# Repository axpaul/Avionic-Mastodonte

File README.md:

# Mastodonte – Séquenceur

**Mastodonte** est un ordinateur de bord, ou plus précisément un **séquenceur**, destiné à orchestrer de manière autonome les événements critiques d’un vol de fusée expérimentale. Il est conçu pour répondre aux exigences du **cahier des charges du C'Space**, et s’intègre à tout projet nécessitant un séquencement fiable, robuste et temps réel.

---

> *© 2025/2026 - Paul Miailhe.*  
> *This material is licensed under the CERN Open Hardware Licence Version 2 - Strongly Reciprocal (CERN-OHL-S). [→ CERN-OHL-S](https://ohwr.org/licences/)*
> > 

---

---

## Fonctionnement

Mastodonte supervise et déclenche en toute autonomie les étapes clés du vol, sans intervention extérieure :

### Détection du décollage
La détection initiale peut se faire par deux méthodes :
- Un **contact jack** (fil coupe-circuit) : un câble fin relie la fusée au sol, et se sectionne au moment du lancement. La coupure génère une interruption matérielle, qui marque le T-0 du vol.
- Un **accéléro-contact** (contacteur à masselotte) peut également déclencher le séquenceur dès détection d’une accélération.

Dans les deux cas, la carte démarre son chronomètre interne pour initier la séquence.

### Fenêtrage temporel autour de l’apogée
Après le décollage, Mastodonte ouvre une **fenêtre temporelle** durant laquelle la détection de l’apogée est autorisée :
- Un signal extérieur, par exemple issu d’un autre système avionique ou d’un capteur, peut être reçu via un **optocoupleur** pour indiquer l’apogée.
- Ce signal n’est pris en compte **que pendant la fenêtre**, afin d’écarter toute détection parasite en dehors de cette phase critique.
- Si aucune détection n’est reçue, un **déclenchement de sécurité** est effectué après un **temps maximal prédéfini** post-apogée, garantissant ainsi l’ouverture du système de récupération.

### Déploiement du système de récupération
En réponse à une détection d’apogée (ou par sécurité en fin de fenêtre), Mastodonte déclenche le système de récupération :
- Par **charge pyrotechnique** (détonateur, coupe-corde, etc.),
- Ou par **moteur DC** (vis de poussée, libération mécanique, etc.).

### Enregistrement des événements critiques
Mastodonte assure un enregistrement précis des points clés du vol :
- Heure de **décollage** (T-0),
- **Début et fin** de la fenêtre d’apogée,
- **Réception (ou absence)** du signal d’apogée,
- **Déclenchement** du système de récupération,
- **Tension batterie** mesurée durant le vol,
- **Événements d’erreur moteur** détectés.

Ce journal d’exécution agit comme une **boîte noire embarquée**, permettant d’analyser a posteriori le bon déroulement de la mission, et d’identifier toute anomalie de comportement.

---

> Mastodonte vise à offrir un **fonctionnement déterministe**, **fiable** et **autonome**, même en l’absence de télémétrie ou de supervision au sol, conformément à l’esprit du **cahier des charges C'Space**.

---

## Architecture & Fonctionnalités

### Alimentation et protections
- Protection contre l’inversion de polarité (MOSFET P **SQD50P04-13L**)
- Protection contre surtensions (**TVS SMAJ14A**)
- Limitation de courant via fusible réarmable
- Régulation de tension (LM340AT : 7.4 V batterie → 5 V)
- Sélection de la source d’alimentation (USB-C ou batterie)
- LED d’indication d’alimentation

### Microcontrôleur RP2040-YD

Mastodonte s’appuie sur la carte **RP2040-YD**, une carte commerciale compacte embarquant un microcontrôleur **RP2040** de Raspberry Pi, accompagnée de ses périphériques essentiels :

- Double cœur **ARM Cortex-M0+** cadencé à 133 MHz
- **128 Mbits (16 MB)** de mémoire flash externe **W25Q128**
- Oscillateur intégré à **12 MHz**
- Interface native **USB-C**
- Format physique compatible **Raspberry Pi Pico**
- Brochage latéral avec **40 broches GPIO** (20 de chaque côté)
- LED RGB **WS2812** intégrée (GPIO23)
- Boutons embarqués :
  - **BOOT**
  - **RESET**
  - **USER KEY** (GPIO24)
- Interface **SWD** pour débogage

La carte **RP2040-YD** est conçue pour venir se **connecter verticalement** sur le PCB principal appelé **BR-Motor** via deux rangées de connecteurs femelles. Une fois assemblée, l'ensemble forme la carte **Mastodonte**, regroupant la logique de contrôle (RP2040-YD) et l’électronique de puissance et d’interface (BR-Motor).

### Interfaces et connectiques
- Connecteurs au format **JST B2B-XH**
- Connexions dédiées pour moteurs, charges pyrotechniques, capteurs et interfaces de communication
- Tensions disponibles : **5 V** et **3.3 V**

---

## Interfaces et E/S

### Commande moteur / Charge pyrotechnique
- 3 drivers **DRV8872DDA** (ponts en H)
  - Jusqu’à **3.6 A** sous **6.5–45 V**
  - Contrôle **PWM**
  - LED de direction pour visualisation sans charge
  - Détection d’erreurs via broche **nFAULT**

### Signaux d’entrée isolés
- **Optocoupleurs ACPL-214** pour isolation galvanique
- Buffers logiques **74HC14** (Schmitt trigger) pour traitement numérique
- Isolation UART et conversion de niveau : **ADuM1281**
- Pull-ups 4.7 kΩ intégrés sur les lignes I²C

### Buzzer de notification
- Pilotage via transistor **BSS138**
- Protection par diode **1N4148**
- Activation par GPIO (IN_BUZZ)

---

## Schéma fonctionnel

---

## Signaux sortants – Carte Mastodonte (RP2040-YD)

| Signal         | Type de signal     | Connecteur        | GPIO RP2040 | Description |
|----------------|--------------------|-------------------|-------------|-------------|
| `IN1_M1`       | PWM / Logique      | J6 (Moteur 1)     | GP14        | Commande H-Bridge moteur/charge 1 |
| `IN2_M1`       | PWM / Logique      | J6 (Moteur 1)     | GP15        | Commande H-Bridge moteur/charge 1 |
| `IN1_M2`       | PWM / Logique      | J7 (Moteur 2)     | GP16        | Commande H-Bridge moteur/charge 2 |
| `IN2_M2`       | PWM / Logique      | J7 (Moteur 2)     | GP17        | Commande H-Bridge moteur/charge 2 |
| `IN1_M3`       | PWM / Logique      | J8 (Moteur 3)     | GP18        | Commande H-Bridge moteur/charge 3 |
| `IN2_M3`       | PWM / Logique      | J8 (Moteur 3)     | GP19         | Commande H-Bridge moteur/charge 3 |
| `IN_BUZZ`      | Logique             | J5 (Buzzer)       | GP2         | Commande du buzzer (MOSFET BSS138) |
| `OUT_N1`       | GPIO                | J10               | GP26        | Sortie numérique non isolée |
| `OUT_N2`       | GPIO                | J10               | GP27        | Sortie numérique non isolée |
| `OUT_N3`       | GPIO                | J10               | GP10        | Sortie numérique non isolée |
| `OUT_N4`       | GPIO                | J11               | GP11        | Sortie numérique non isolée |
| `OUT_N5`       | GPIO                | J11               | GP12        | Sortie numérique non isolée |
| `OUT_N6`       | GPIO                | J11               | GP13        | Sortie numérique non isolée |
| `OUT_ISO_N3`   | GPIO isolée         | J13 (Opto)        | GP3         | Sortie isolée via optocoupleur |
| `OUT_ISO_N4`   | GPIO isolée         | J13 (Opto)        | GP4         | Sortie isolée via optocoupleur |
| `SDA`          | I²C (données)       | J12 (I²C)         | GP8         | Bus I²C données (avec pull-up) |
| `SCL`          | I²C (horloge)       | J12 (I²C)         | GP9         | Bus I²C horloge (avec pull-up) |
| `IN_ISO_N1`    | UART (émission)     | J9 (UART)         | GP0         | Émission isolée série vers modules externes |
| `OUT_ISO_N2`   | UART (réception)    | J9 (UART)         | GP1         | Réception isolée série depuis modules externes |
| `VCC_BAT`      | Alimentation        | J2 / J3 (OUT PWR) | —           | Tension batterie (après filtrage) exposée |
| `+5V`          | Alimentation régulée| J2 / J3 / I²C     | —           | Tension 5 V régulée disponible |
| `+3.3V`        | Alimentation logique| Tous connecteurs  | —           | Tension logique (niveau RP2040) |

> Tous les signaux sont sur le standart CMOS 3.3 V côté logique.

## RP2040-YD PINOUT

---

## Caractéristiques mécaniques

- Dimensions : **100 × 40 mm**
- Épaisseur maximale : **18.13 mm**
- Trous de fixation : 4 × Ø3.2 mm
- Masse sans support : **37 g**
- Fichier **STEP 3D** disponible ici : [`Mechanical/BR-Motor.step`](Mechanical/BR-Motor.step)

---

## Ressources utiles

Composants utilisés sur la carte Mastodonte, avec leurs fiches techniques officielles :

| Composant | Rôle dans le système | Fiche technique |
|----------|----------------------|-----------------|
| **DRV8872** | Driver de moteur DC (pont en H jusqu’à 3.6 A) | [→ Datasheet TI](https://www.ti.com/lit/ds/symlink/drv8872.pdf) |
| **RP2040** | Microcontrôleur principal double cœur | [→ Datasheet Raspberry Pi](https://www.raspberrypi.com/documentation/microcontrollers/rp2040.html) |
| **ACPL-214** | Optocoupleur pour isolation galvanique des signaux d’entrée | [→ Datasheet Broadcom](https://www.broadcom.com/products/optocouplers/industrial-plastic/acpl-214) |
| **TLP292(TPL,E** | Optocoupleur pour isolation galvanique des signaux d’entrée | [→ Datasheet Toshiba](https://toshiba.semicon-storage.com/info/TLP292_datasheet_en_20191129.pdf?did=14425&prodName=TLP292) |
| **74HC14** | Buffer logique à trigger de Schmitt pour traitement des signaux numériques | [→ Datasheet TI](https://www.ti.com/lit/ds/symlink/sn74hc14.pdf?ts=1743611017766) |
| **ADuM1281** | Isolateur numérique double canal pour signaux UART | [→ Datasheet Analog Devices](https://www.analog.com/media/en/technical-documentation/data-sheets/ADuM1280_1281_1285_1286.pdf) |
| **LM340AT** | Régulateur de tension linéaire 5V | [→ Datasheet TI](https://www.ti.com/lit/ds/symlink/lm340.pdf) |
| **1812L260/16MR** | Fusible réarmable pour limitation de courant | [→ Datasheet Littelfuse](https://www.littelfuse.com/assetdocs/resettable-ptcs-1812l-datasheet?assetguid=ca5c80cb-504e-4a8a-8e74-0107520a1717) |
| **SQD50P04-13L** | MOSFET P pour protection contre l’inversion de polarité | [→ Datasheet Vishay](https://www.vishay.com/docs/65157/sqd50p04-13l.pdf) |
| **BSS138** | Transistor N-MOS pour commutation de charges faibles (buzzer, etc.) | [→ Datasheet OnSemi](https://www.onsemi.com/pdf/datasheet/bss138-d.pdf) |

> Sur la production 02/03/2025, les optocoupleurs utilisés sont les TLP292(TPL,E).

---

# [OPTION] : BR Mini Sensor

La **BR Mini Sensor** est une carte mezzanine entièrement compatible avec la Raspberry Pi Pico. Il s'agit d'un **COMPLEMENT**. Le stack sans fonctionne parfaitement sans, mais cet ajout permet d'étendre ses capacités.
Elle embarque une suite de capteurs communicant via le bus **I²C** :
* **Un accéléromètre 3 axes & un gyromètre 3 axes** (IMU) : Basés sur le composant **LSM6DSL** de STMicroelectronics.
* **Un capteur de pression** permettant de mesurer l'altitude : Basé sur le composant **LPS22HB** de STMicroelectronics.

La carte BR Mini Sensor vous permettra, moyennant un peu de code, de mesurer et d'enregistrer les paramètres de vol de votre fusée afin d'en estimer la trajectoire.
Pour plus de détails, consultez la documentation officielle : [Wiki BR Mini Sensor](https://berryrocket.com/wiki/BR_Mini_Sensor).

## Configuration matérielle et précautions

Lors de l'intégration de la carte, une attention particulière doit être portée à la gestion des broches d'interruption :

* **Isolement des interruptions (INT1 / INT2) :** Il est nécessaire de prévoir le **dessoudage de certaines résistances 0R** sur la carte pour les lignes `INT1` et `INT2` de l'IMU.
* **Prévention des conflits :** Cette modification permet d'éviter de polluer d'autres pins de la carte BR-Motor et d'interférer avec l'**optocoupleur** ou le signal **Nfault du moteur 3**.

---

## Test Fly Video

La vidéo de qualification de Mastodonte pour le projet Diamant :

### [Visionner le Test Avionique Mastodonte sur YouTube](https://www.youtube.com/watch?v=LKwvPUTVWk4)

<p align="center">
  
</p>

*Test des systèmes embarqués de la fusée Mastodonte.*

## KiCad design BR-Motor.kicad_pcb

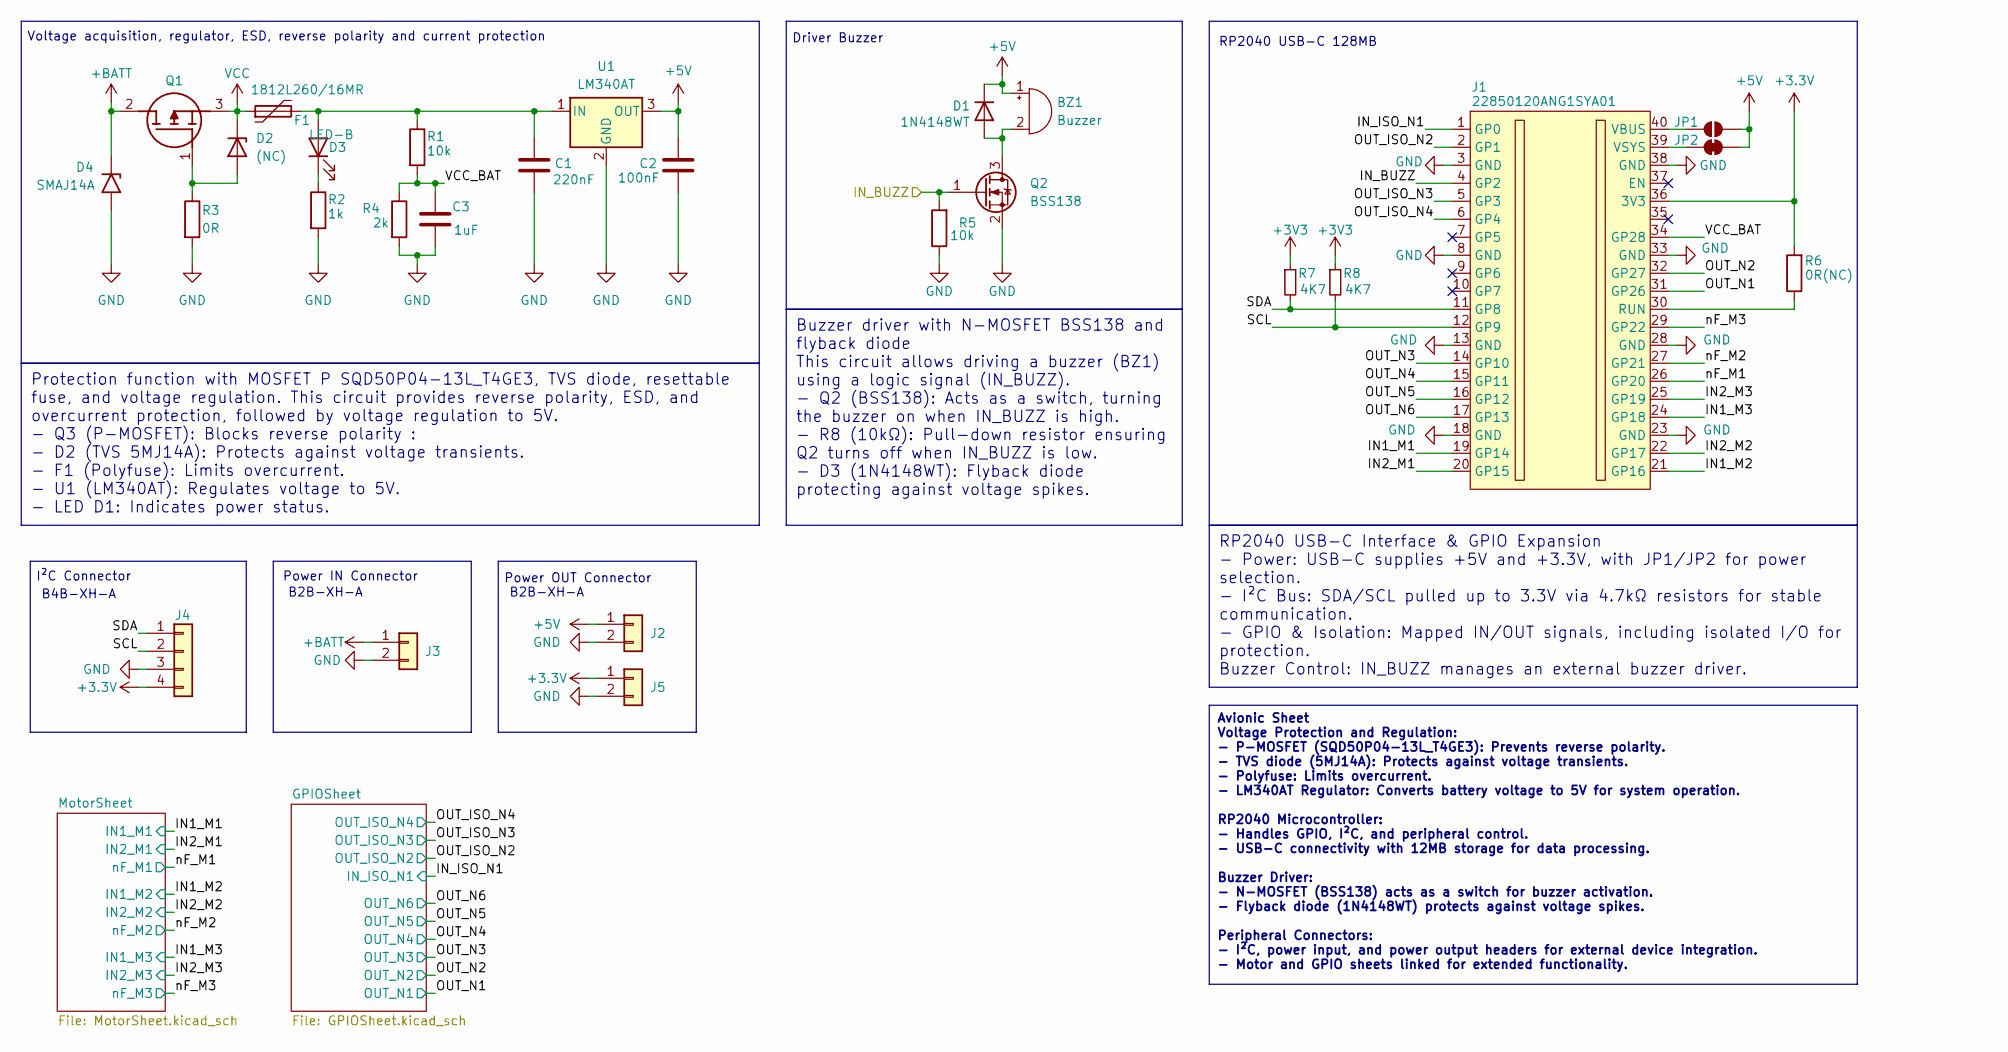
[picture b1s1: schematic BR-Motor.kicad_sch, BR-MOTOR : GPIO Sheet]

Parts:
BZ1: Buzzer; Buzzer_12x9.5RM7.6
C1: 220nF; C_1206_3216Metric
C2: 100nF; C_1206_3216Metric
C3: 1uF; C_0603_1608Metric
D1: 1N4148WT; D_SOD-523
D2: (NC); D_0805_2012Metric
D3: LED-B; LED_0603_1608Metric
D4: SMAJ14A; D_SMA
F1: 1812L260/16MR; Fuse_1812_4532Metric
J1: 22850120ANG1SYA01; RPi_Pico_TH
J2, J3, J5: Conn_01x02; JST_XH_B2B-XH-A_1x02_P2.50mm_Vertical
J4: Conn_01x04; JST_XH_B4B-XH-A_1x04_P2.50mm_Vertical
JP1: SolderJumper_2_Open; SolderJumper-2_P1.3mm_Open_RoundedPad1.0x1.5mm
JP2: SolderJumper_2_Bridged; SolderJumper-2_P1.3mm_Bridged_RoundedPad1.0x1.5mm
Q1: SQD50P04-13L_T4GE3; SQD50P0413L_T4GE3; Manufacturer_Part_Number SQD50P04-13L_T4GE3; Mouser Part Number 78-SQD50P04-13LT4GE3
Q2: BSS138; SOT-23
R1, R5: 10k; R_0603_1608Metric
R2: 1k; R_0603_1608Metric
R3: 0R; R_0603_1608Metric
R4: 2k; R_0603_1608Metric
R6: 0R(NC); R_0603_1608Metric
R7, R8: 4K7; R_0603_1608Metric
U1: LM340AT; TO-220-3_Horizontal_TabDown

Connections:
+3.3V: J1.36 (3V3), J4.4, J5.1, R6.2; also elsewhere on the board
+3V3: R7.1, R8.1
+5V: BZ1.1 (+), C2.1, D1.1 (K), J2.1, JP1.2 (B), JP2.2 (B), U1.3 (OUT); also elsewhere on the board
+BATT: D4.1 (A1), J3.1, Q1.2 (D)
/IN1_M1: J1.19 (GP14); also elsewhere on the board
/IN1_M2: J1.21 (GP16); also elsewhere on the board
/IN1_M3: J1.24 (GP18); also elsewhere on the board
/IN2_M1: J1.20 (GP15); also elsewhere on the board
/IN2_M2: J1.22 (GP17); also elsewhere on the board
/IN2_M3: J1.25 (GP19); also elsewhere on the board
/IN_BUZZ: J1.4 (GP2), Q2.1 (G), R5.2
/IN_ISO_N1: J1.1 (GP0); also elsewhere on the board
/OUT_ISO_N2: J1.2 (GP1); also elsewhere on the board
/OUT_ISO_N3: J1.5 (GP3); also elsewhere on the board
/OUT_ISO_N4: J1.6 (GP4); also elsewhere on the board
/OUT_N1: J1.31 (GP26); also elsewhere on the board
/OUT_N2: J1.32 (GP27); also elsewhere on the board
/OUT_N3: J1.14 (GP10); also elsewhere on the board
/OUT_N4: J1.15 (GP11); also elsewhere on the board
/OUT_N5: J1.16 (GP12); also elsewhere on the board
/OUT_N6: J1.17 (GP13); also elsewhere on the board
/SCL: J1.12 (GP9), J4.2, R8.2
/SDA: J1.11 (GP8), J4.1, R7.2
/VCC_BAT: C3.1, J1.34 (GP28), R1.2, R4.1
/nF_M1: J1.26 (GP20); also elsewhere on the board
/nF_M2: J1.27 (GP21); also elsewhere on the board
/nF_M3: J1.29 (GP22); also elsewhere on the board
GND: C1.2, C2.2, C3.2, D4.2 (A2), J1.3 (GND), J1.8 (GND), J1.13 (GND), J1.18 (GND), J1.23 (GND), J1.28 (GND), J1.33 (GND), J1.38 (GND), J2.2, J3.2, J4.3, J5.2, Q2.2 (S), R2.2, R3.2, R4.2, R5.1, U1.2 (GND); also elsewhere on the board
unnamed: BZ1.2 (-), D1.2 (A), Q2.3 (D)
unnamed: D2.2 (A), Q1.1 (G), R3.1
unnamed: C1.1, D3.2 (A), F1.2, R1.1, U1.1 (IN)
unnamed: D3.1 (K), R2.1
unnamed: J1.30 (RUN), R6.1
unnamed: J1.40 (VBUS), JP1.1 (A)
unnamed: J1.39 (VSYS), JP2.1 (A)
VCC: D2.1 (K), F1.1, Q1.3 (S); also elsewhere on the board

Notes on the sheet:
Avionic Sheet Voltage Protection and Regulation: - P-MOSFET (SQD50P04-13L_T4GE3): Prevents reverse polarity. - TVS diode (5MJ14A): Protects against voltage transients. - Polyfuse: Limits overcurrent. - LM340AT Regulator: Converts battery voltage to 5V for system operation. RP2040 Microcontroller: -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
Protection function with MOSFET P SQD50P04-13L_T4GE3, TVS diode, resettable fuse, and voltage regulation. This circuit provides reverse polarity, ESD, and overcurrent protection, followed by voltage regulation to 5V. - Q3 (P-MOSFET): Blocks reverse polarity : - D2 (TVS 5MJ14A): Protects against vol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
RP2040 USB-C Interface & GPIO Expansion - Power: USB-C supplies +5V and +3.3V, with JP1/JP2 for power selection. - I²C Bus: SDA/SCL pulled up to 3.3V via 4.7kΩ resistors for stable communication. - GPIO & Isolation: Mapped IN/OUT signals, including isolated I/O for protection. Buzzer Control: IN_BU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
Buzzer driver with N-MOSFET BSS138 and flyback diode This circuit allows driving a buzzer (BZ1) using a logic signal (IN_BUZZ). - Q2 (BSS138): Acts as a switch, turning the buzzer on when IN_BUZZ is high. - R8 (10kΩ): Pull-down resistor ensuring Q2 turns off when IN_BUZZ is low. - D3 (1N4148WT): Fl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
I²C Connector
Voltage acquisition, regulator, ESD, reverse polarity and current protection
Power IN Connector
Power OUT Connector
B2B-XH-A
Driver Buzzer
B4B-XH-A
RP2040 USB-C 128MB

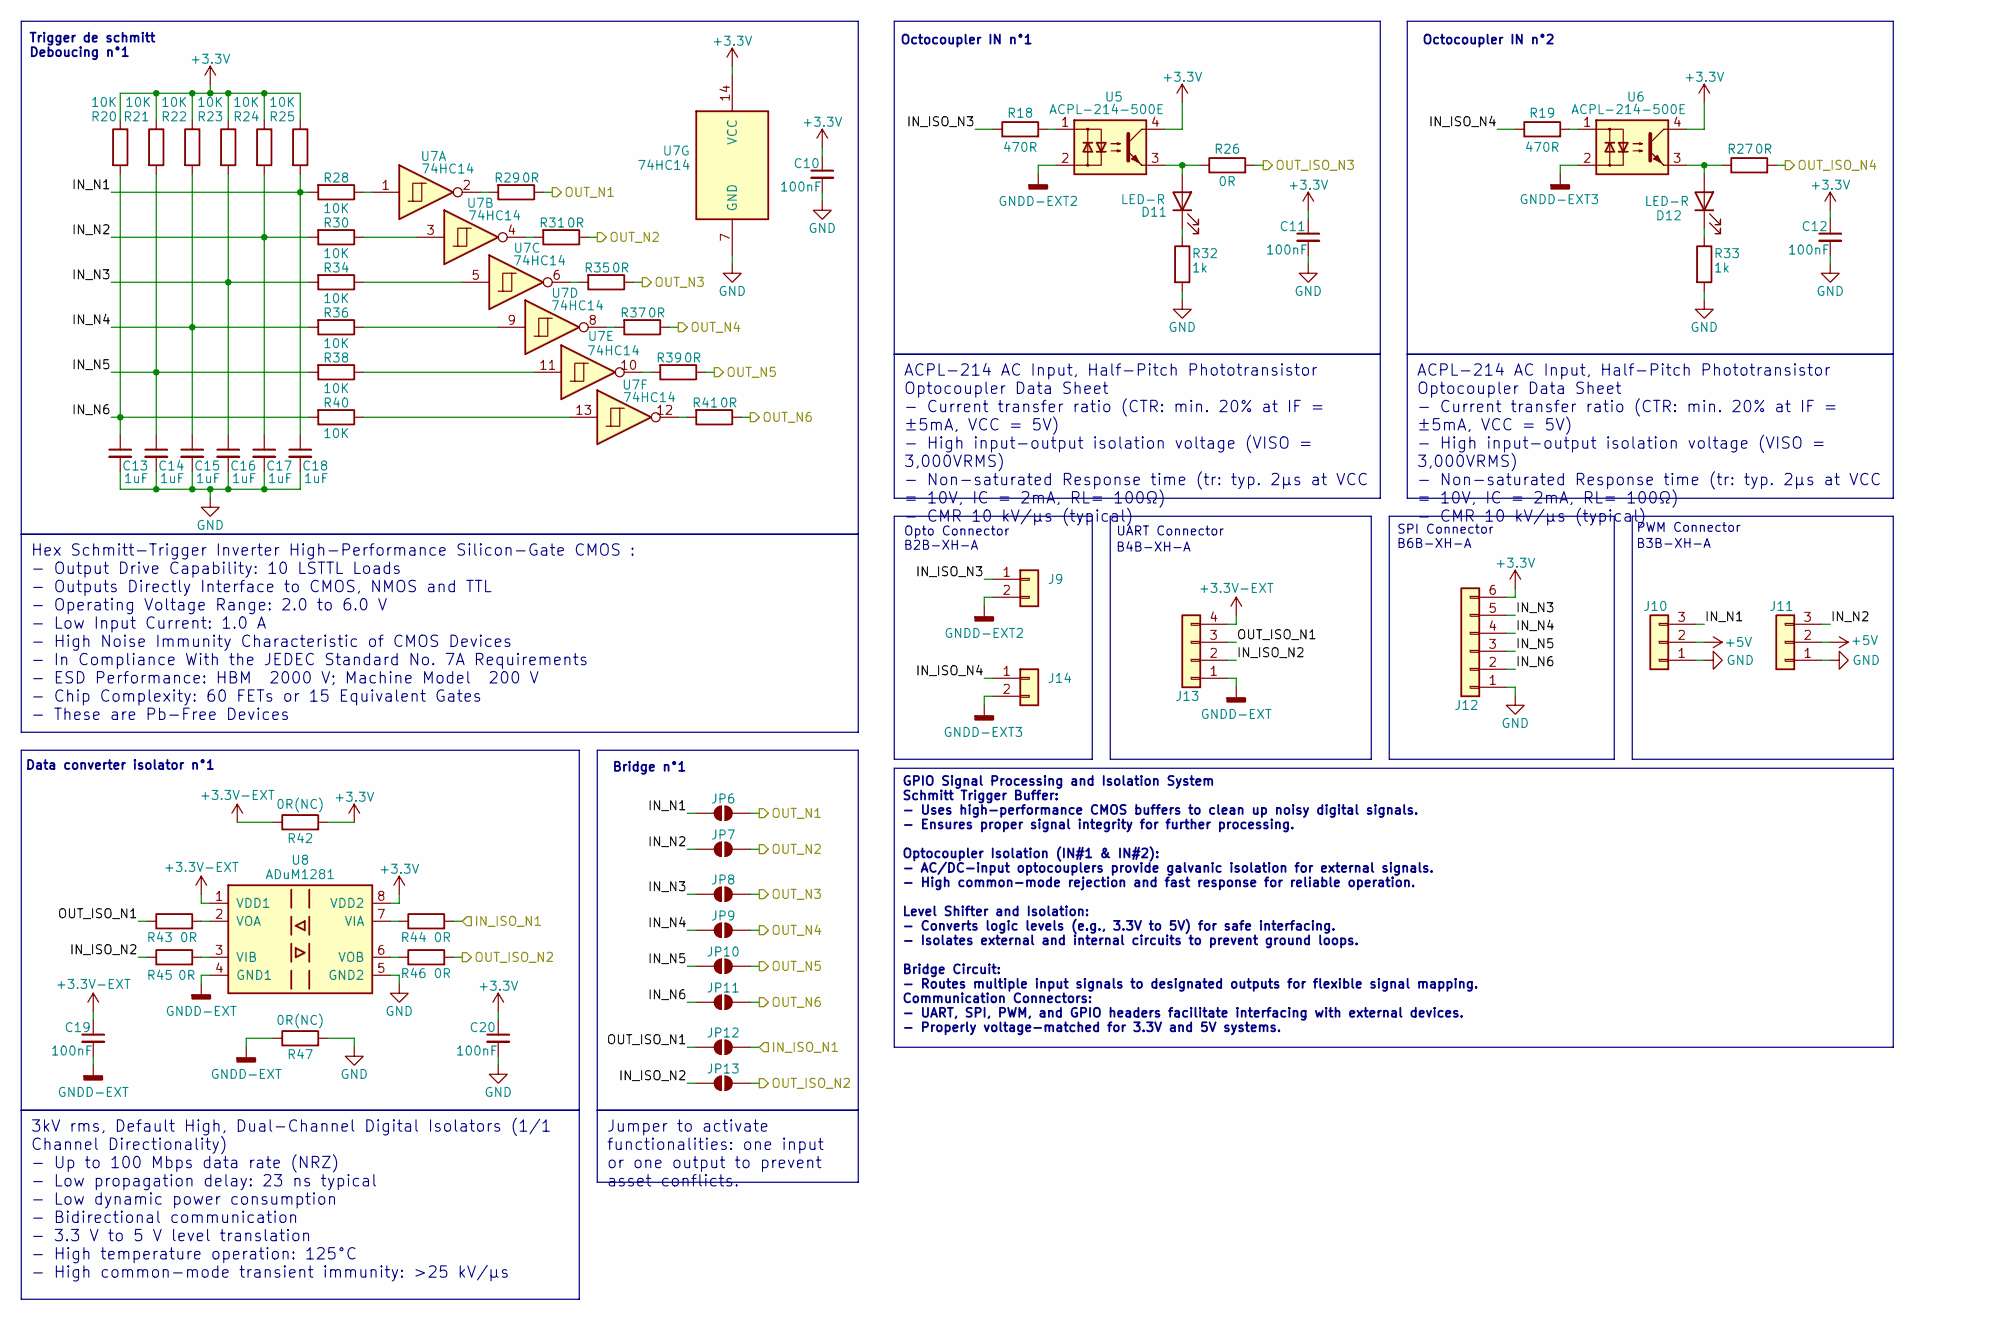
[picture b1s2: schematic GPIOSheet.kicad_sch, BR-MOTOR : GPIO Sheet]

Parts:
C10, C11, C12, C19, C20: 100nF; C_0603_1608Metric
C13, C14, C15, C16, C17, C18: 1uF; C_0603_1608Metric
D11, D12: LED-R; LED_0603_1608Metric
J9, J14: Conn_01x02; JST_XH_B2B-XH-A_1x02_P2.50mm_Vertical
J10, J11: Conn_01x03; JST_XH_B3B-XH-A_1x03_P2.50mm_Vertical
J12: Conn_01x06; JST_XH_B6B-XH-A_1x06_P2.50mm_Vertical
J13: Conn_01x04; JST_XH_B4B-XH-A_1x04_P2.50mm_Vertical
JP6, JP7, JP8, JP9, JP10, JP11, JP12, JP13: 0R(NC); R_0603_1608Metric
R18, R19: 470R; R_0603_1608Metric
R20, R21, R22, R23, R24, R25, R28, R30, R34, R36, R38, R40: 10K; R_0603_1608Metric
R26, R27, R29, R31, R35, R37, R39, R41, R43, R44, R45, R46: 0R; R_0603_1608Metric
R32, R33: 1k; R_0603_1608Metric
R42, R47: 0R(NC); R_0603_1608Metric
U5, U6: ACPL-214-500E; SOP-4_4.4x2.6mm_P1.27mm
U7: 74HC14; SOIC-14_3.9x8.7mm_P1.27mm
U8: ADuM1281; SOIC-8_3.9x4.9mm_P1.27mm

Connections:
+3.3V: C10.1, C11.1, C12.1, C20.1, J12.6, R20.1, R21.1, R22.1, R23.1, R24.1, R25.1, R42.2, U5.4, U6.4, U7.14 (VCC), U8.8 (VDD2); also elsewhere on the board
+3.3V-EXT: C19.1, J13.4, R42.1, U8.1 (VDD1)
+5V: J10.2, J11.2; also elsewhere on the board
/GPIOSheet/IN_ISO_N2: J13.2, JP13.1 (A), R45.1
/GPIOSheet/IN_ISO_N3: J9.1, R18.1
/GPIOSheet/IN_ISO_N4: J14.1, R19.1
/GPIOSheet/IN_N1: C18.1, J10.3, JP6.1 (A), R25.2, R28.2
/GPIOSheet/IN_N2: C17.1, J11.3, JP7.1 (A), R24.2, R30.2
/GPIOSheet/IN_N3: C16.1, J12.5, JP8.1 (A), R23.2, R34.2
/GPIOSheet/IN_N4: C15.1, J12.4, JP9.1 (A), R22.2, R36.2
/GPIOSheet/IN_N5: C14.1, J12.3, JP10.1 (A), R21.2, R38.2
/GPIOSheet/IN_N6: C13.1, J12.2, JP11.1 (A), R20.2, R40.2
/GPIOSheet/OUT_ISO_N1: J13.3, JP12.1 (A), R43.1
/IN_ISO_N1: JP12.2 (B), R44.2; also elsewhere on the board
/OUT_ISO_N2: JP13.2 (B), R46.2; also elsewhere on the board
/OUT_ISO_N3: R26.2; also elsewhere on the board
/OUT_ISO_N4: R27.2; also elsewhere on the board
/OUT_N1: JP6.2 (B), R29.1; also elsewhere on the board
/OUT_N2: JP7.2 (B), R31.1; also elsewhere on the board
/OUT_N3: JP8.2 (B), R35.1; also elsewhere on the board
/OUT_N4: JP9.2 (B), R37.1; also elsewhere on the board
/OUT_N5: JP10.2 (B), R39.1; also elsewhere on the board
/OUT_N6: JP11.2 (B), R41.1; also elsewhere on the board
GND: C10.2, C11.2, C12.2, C13.2, C14.2, C15.2, C16.2, C17.2, C18.2, C20.2, J10.1, J11.1, J12.1, R32.2, R33.2, R47.2, U7.7 (GND), U8.5 (GND2); also elsewhere on the board
GNDD-EXT: C19.2, J13.1, R47.1, U8.4 (GND1)
GNDD-EXT2: J9.2, U5.2
GNDD-EXT3: J14.2, U6.2
unnamed: D11.2 (A), R26.1, U5.3
unnamed: D11.1 (K), R32.1
unnamed: D12.2 (A), R27.1, U6.3
unnamed: D12.1 (K), R33.1
unnamed: R18.2, U5.1
unnamed: R19.2, U6.1
unnamed: R28.1, U7.1
unnamed: R29.2, U7.2
unnamed: R30.1, U7.3
unnamed: R31.2, U7.4
unnamed: R34.1, U7.5
unnamed: R35.2, U7.6
unnamed: R36.1, U7.9
unnamed: R37.2, U7.8
unnamed: R38.1, U7.11
unnamed: R39.2, U7.10
unnamed: R40.1, U7.13
unnamed: R41.2, U7.12
unnamed: R44.1, U8.7 (VIA)
unnamed: R45.2, U8.3 (VIB)
unnamed: R43.2, U8.2 (VOA)
unnamed: R46.1, U8.6 (VOB)

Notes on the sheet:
Hex Schmitt−Trigger Inverter High−Performance Silicon−Gate CMOS : - Output Drive Capability: 10 LSTTL Loads - Outputs Directly Interface to CMOS, NMOS and TTL - Operating Voltage Range: 2.0 to 6.0 V - Low Input Current: 1.0 A - High Noise Immunity Characteristic of CMOS Devices - In Compliance With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
3kV rms, Default High, Dual-Channel Digital Isolators (1/1 Channel Directionality) - Up to 100 Mbps data rate (NRZ) - Low propagation delay: 23 ns typical - Low dynamic power consumption - Bidirectional communication - 3.3 V to 5 V level translation - High temperature operation: 125°C - High common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
ACPL-214 AC Input, Half-Pitch Phototransistor Optocoupler Data Sheet - Current transfer ratio (CTR: min. 20% at IF = ±5mA, VCC = 5V) - High input-output isolation voltage (VISO = 3,000VRMS) - Non-saturated Response time (tr: typ. 2μs at VCC = 10V, IC = 2mA, RL= 100Ω) - CMR 10 kV/μs (typical)
Jumper to activate functionalities: one input or one output to prevent asset conflicts.
GPIO Signal Processing and Isolation System Schmitt Trigger Buffer: - Uses high-performance CMOS buffers to clean up noisy digital signals. - Ensures proper signal integrity for further processing. Optocoupler Isolation (IN#1 & IN#2): - AC/DC-input optocouplers provide galvanic isolation for extern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
Opto Connector
Octocoupler IN n°2
Octocoupler IN n°1
PWM Connector
UART Connector
Bridge n°1
B4B-XH-A
SPI Connector
B3B-XH-A
B2B-XH-A
Data converter isolator n°1
B6B-XH-A
Trigger de schmitt Deboucing n°1

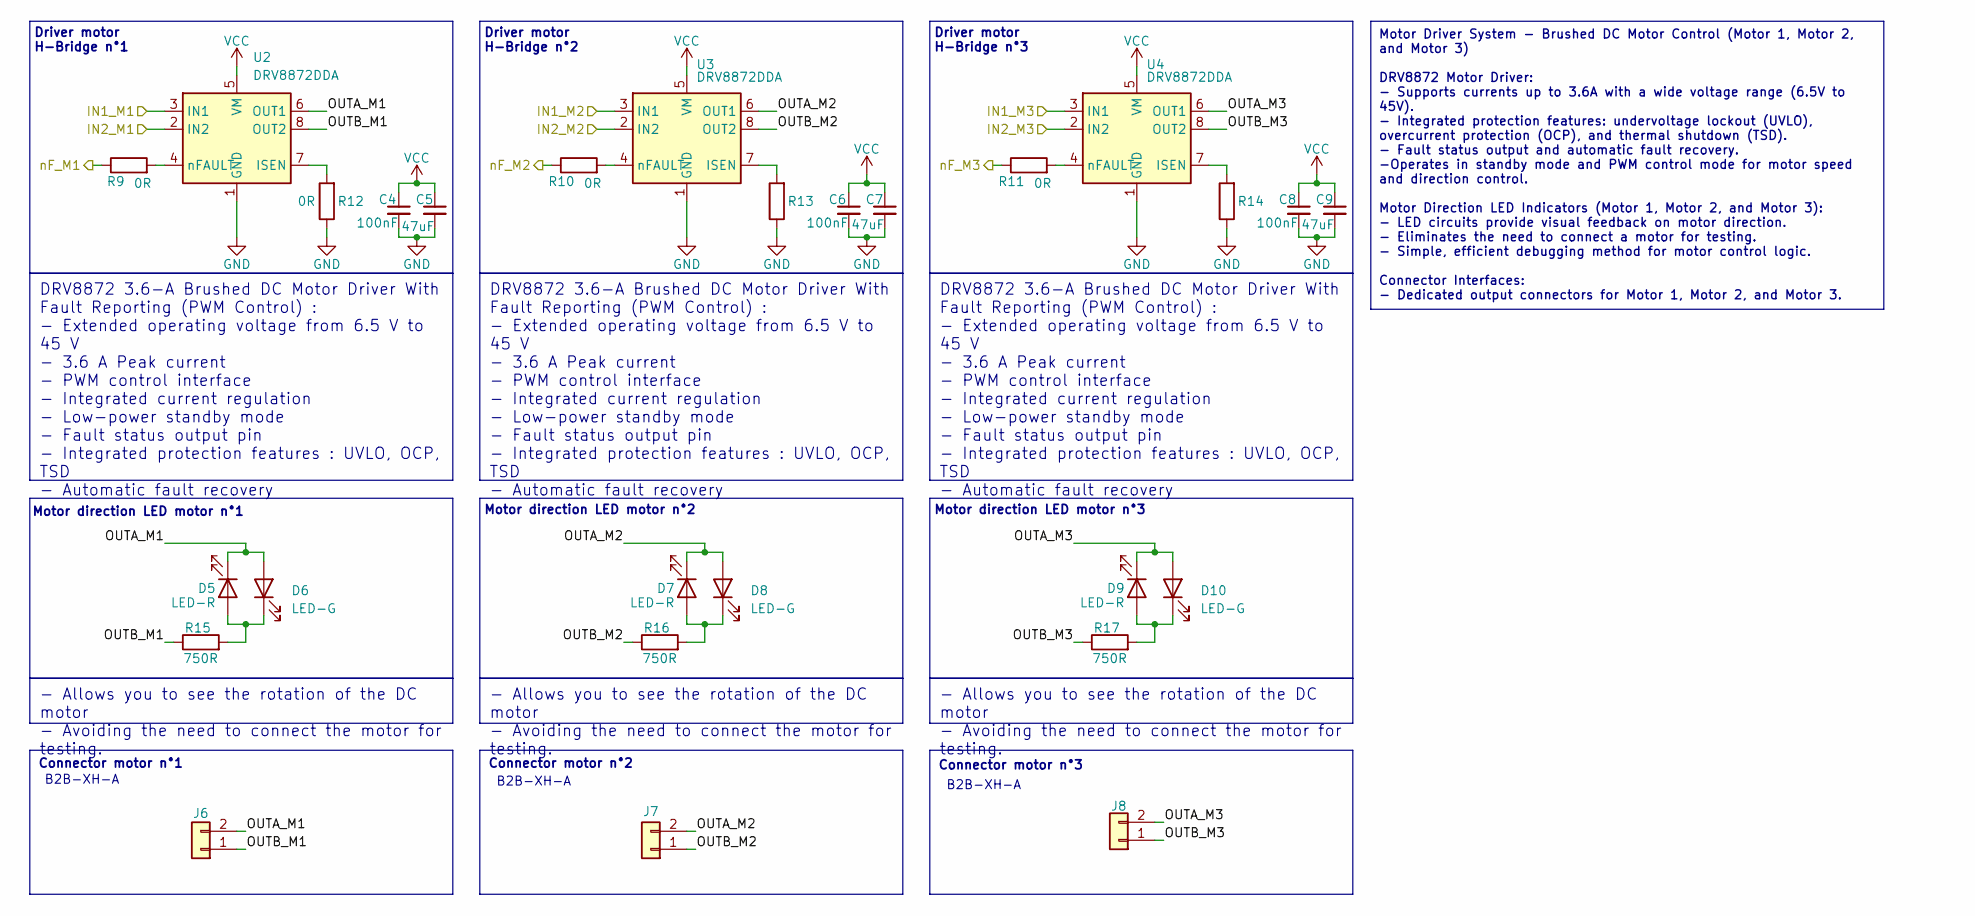
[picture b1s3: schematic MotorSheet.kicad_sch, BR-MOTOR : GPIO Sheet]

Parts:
C4, C6, C8: 100nF; C_0603_1608Metric
C5, C7, C9: 47uF; C_1206_3216Metric
D5, D7, D9: LED-R; LED_0603_1608Metric
D6, D8, D10: LED-G; LED_0603_1608Metric
J6, J7, J8: Conn_01x02; JST_XH_B2B-XH-A_1x02_P2.50mm_Vertical
R9, R10, R11, R12, R13, R14: 0R; R_0603_1608Metric
R15, R16, R17: 750R; R_0603_1608Metric
U2, U3, U4: DRV8872DDA; Texas_HTSOP-8-1EP_3.9x4.9mm_P1.27mm_EP2.95x4.9mm_Mask2.4x3.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

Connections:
/IN1_M1: U2.3 (IN1); also elsewhere on the board
/IN1_M2: U3.3 (IN1); also elsewhere on the board
/IN1_M3: U4.3 (IN1); also elsewhere on the board
/IN2_M1: U2.2 (IN2); also elsewhere on the board
/IN2_M2: U3.2 (IN2); also elsewhere on the board
/IN2_M3: U4.2 (IN2); also elsewhere on the board
/MotorSheet/OUTA_M1: D5.1 (K), D6.2 (A), J6.2, U2.6 (OUT1)
/MotorSheet/OUTA_M2: D7.1 (K), D8.2 (A), J7.2, U3.6 (OUT1)
/MotorSheet/OUTA_M3: D9.1 (K), D10.2 (A), J8.2, U4.6 (OUT1)
/MotorSheet/OUTB_M1: J6.1, R15.1, U2.8 (OUT2)
/MotorSheet/OUTB_M2: J7.1, R16.1, U3.8 (OUT2)
/MotorSheet/OUTB_M3: J8.1, R17.1, U4.8 (OUT2)
/nF_M1: R9.1; also elsewhere on the board
/nF_M2: R10.1; also elsewhere on the board
/nF_M3: R11.1; also elsewhere on the board
GND: C4.2, C5.2, C6.2, C7.2, C8.2, C9.2, R12.1, R13.1, R14.1, U2.1 (GND), U2.9 (GND), U3.1 (GND), U3.9 (GND), U4.1 (GND), U4.9 (GND); also elsewhere on the board
unnamed: D5.2 (A), D6.1 (K), R15.2
unnamed: D7.2 (A), D8.1 (K), R16.2
unnamed: D9.2 (A), D10.1 (K), R17.2
unnamed: R12.2, U2.7 (ISEN)
unnamed: R9.2, U2.4 (nFAULT)
unnamed: R13.2, U3.7 (ISEN)
unnamed: R10.2, U3.4 (nFAULT)
unnamed: R14.2, U4.7 (ISEN)
unnamed: R11.2, U4.4 (nFAULT)
VCC: C4.1, C5.1, C6.1, C7.1, C8.1, C9.1, U2.5 (VM), U3.5 (VM), U4.5 (VM); also elsewhere on the board

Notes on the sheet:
Motor Driver System - Brushed DC Motor Control (Motor 1, Motor 2, and Motor 3) DRV8872 Motor Driver: - Supports currents up to 3.6A with a wide voltage range (6.5V to 45V). - Integrated protection features: undervoltage lockout (UVLO), overcurrent protection (OCP), and thermal shutdown (TSD). - Fau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
- Allows you to see the rotation of the DC motor - Avoiding the need to connect the motor for testing.
DRV8872 3.6-A Brushed DC Motor Driver With Fault Reporting (PWM Control) : - Extended operating voltage from 6.5 V to 45 V - 3.6 A Peak current - PWM control interface - Integrated current regulation - Low-power standby mode - Fault status output pin - Integrated protection features : UVLO, OCP, TS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
Driver motor H-Bridge n°3
Connector motor n°2
Driver motor H-Bridge n°1
B2B-XH-A
Connector motor n°3
Driver motor H-Bridge n°2
Motor direction LED motor n°1
Motor direction LED motor n°2
Motor direction LED motor n°3
Connector motor n°1

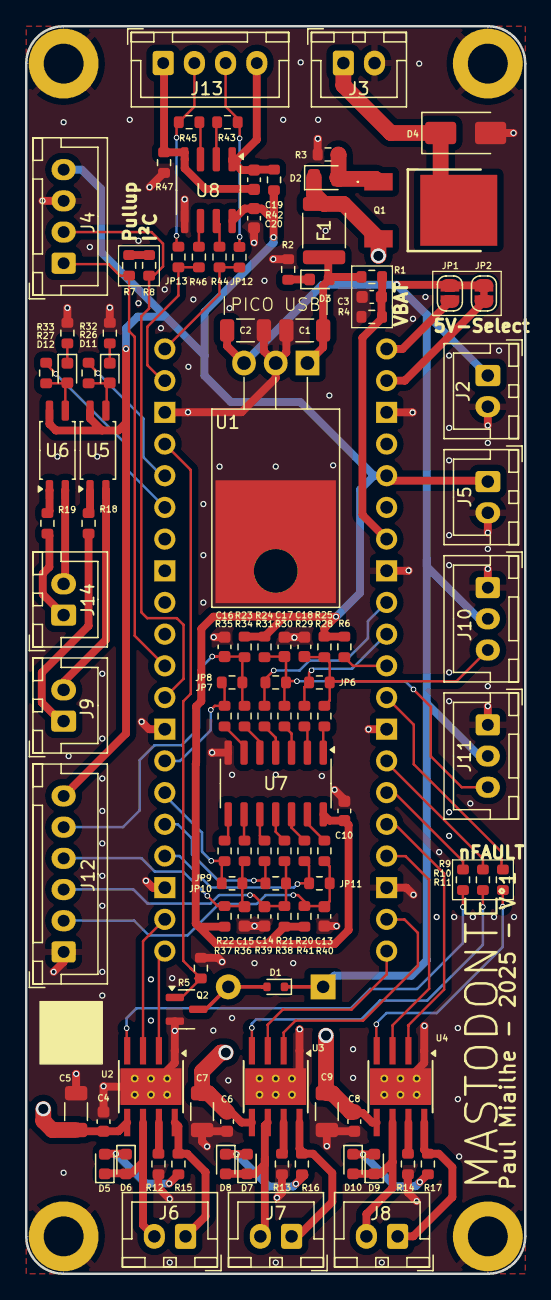
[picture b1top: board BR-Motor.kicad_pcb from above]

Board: 4 copper layers, 40.0 x 100.0 mm, 117 parts (1 on the bottom side), 87 nets.

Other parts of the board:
REF1, REF2, REF3, REF4: MountingHole_3.2mm_M3_DIN965_Pad

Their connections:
GND: REF1.1, REF2.1, REF3.1, REF4.1; also elsewhere on the board

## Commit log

2025-04-01 add files
2025-04-01 reorganize files
2025-04-01 rename zip
2025-04-01 rename folders
2025-04-01 git format image
2025-04-01 remove
2025-04-01 update folders
2025-04-01 Add synoptique
2025-04-01 update synoptique
2025-04-05 Update PDF shematic
2025-04-22 Create LICENCE-HARDWARE
2026-01-26 Update copyright and licensing information in README
2026-06-16 Update README with BR Mini Sensor information
    Added details about the BR Mini Sensor module and hardware configuration precautions.
2026-06-16 Revise BR Mini Sensor description and add image
    Updated the BR Mini Sensor section to clarify its compatibility and added an image link.
2026-06-16 Adjust image width for BR Mini Sensor
    Updated image width in README for better display.
2026-06-16 Add CERN-OHL-S license badge to README
    Added license badge for CERN Open Hardware Licence.

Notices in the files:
README.md:
License: CERN-OHL-S
